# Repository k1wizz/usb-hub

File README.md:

# Usb hub
first try at usb hub using fallout tutorial
https://fallout.hackclub.com/docs/guided-projects/usb-hub
ps i made this on kicad instead of easyeda rahh

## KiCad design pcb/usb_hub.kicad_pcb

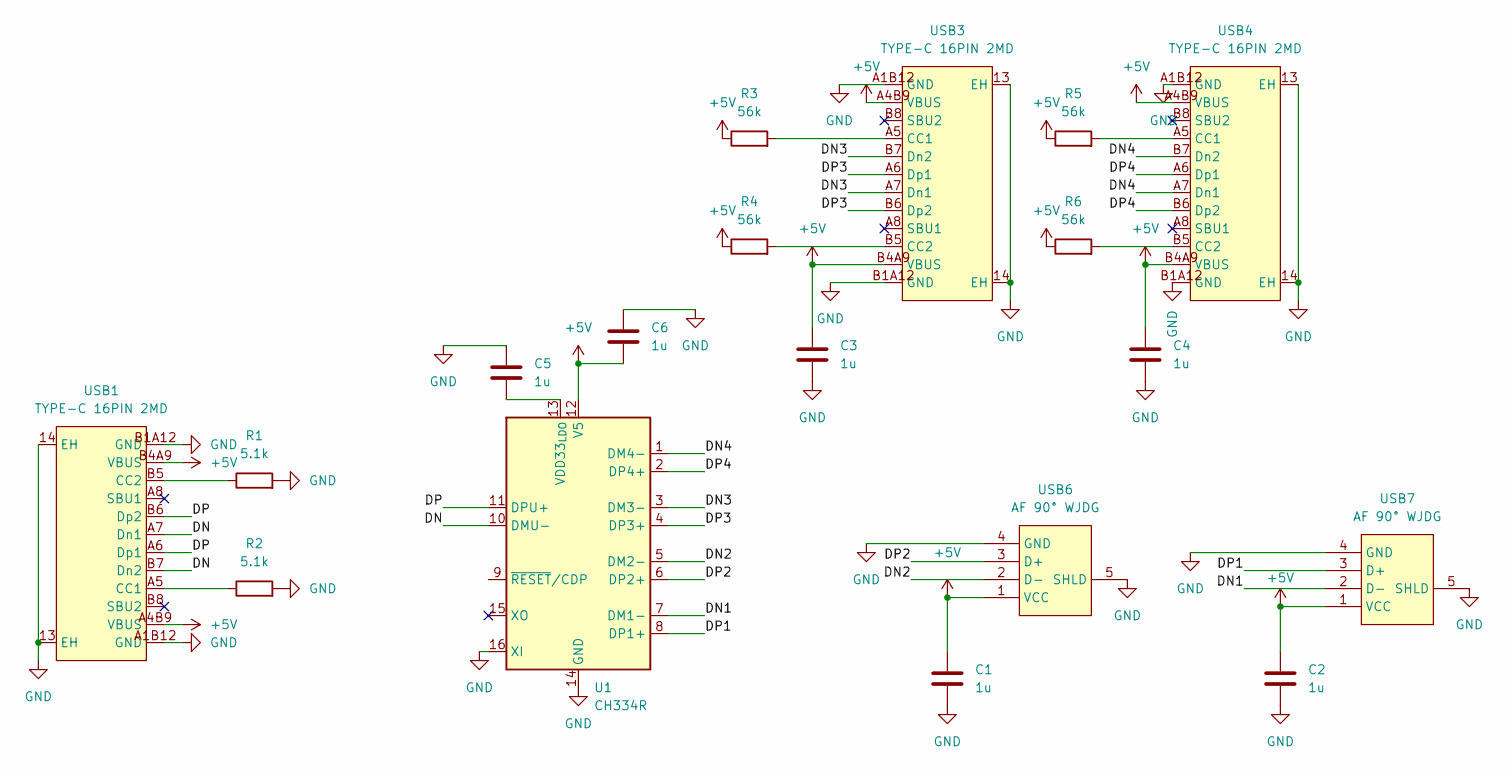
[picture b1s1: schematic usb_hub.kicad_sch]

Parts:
C1, C2, C3, C4, C5, C6: 1u; C_0603_1608Metric
R1, R2: 5.1k; R_0603_1608Metric
R3, R4, R5, R6: 56k; R_0603_1608Metric
U1: CH334R; QSOP-16_3.9x4.9mm_P0.635mm
USB1, USB3, USB4: TYPE-C 16PIN 2MD; USB-C-SMD_TYPE-C-16PIN-2MD-073; MPN TYPE-C 16PIN 2MD(073); LCSC Part C2765186
USB6, USB7: AF 90° WJDG; USB-A-TH_AF-WJDG; MPN AF 90° WJDG; LCSC Part C456018

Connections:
+5V: C1.1, C2.1, C3.1, C4.1, C6.1, R3.1, R4.1, R5.1, R6.1, U1.12 (V5), USB1.A4B9 (VBUS), USB1.B4A9 (VBUS), USB3.A4B9 (VBUS), USB3.B4A9 (VBUS), USB4.A4B9 (VBUS), USB4.B4A9 (VBUS), USB6.1 (VCC), USB7.1 (VCC)
/DN: U1.10 (DMU-), USB1.A7 (Dn1), USB1.B7 (Dn2)
/DN1: U1.7 (DM1-), USB7.2 (D-)
/DN2: U1.5 (DM2-), USB6.2 (D-)
/DN3: U1.3 (DM3-), USB3.A7 (Dn1), USB3.B7 (Dn2)
/DN4: U1.1 (DM4-), USB4.A7 (Dn1), USB4.B7 (Dn2)
/DP: U1.11 (DPU+), USB1.A6 (Dp1), USB1.B6 (Dp2)
/DP1: U1.8 (DP1+), USB7.3 (D+)
/DP2: U1.6 (DP2+), USB6.3 (D+)
/DP3: U1.4 (DP3+), USB3.A6 (Dp1), USB3.B6 (Dp2)
/DP4: U1.2 (DP4+), USB4.A6 (Dp1), USB4.B6 (Dp2)
GND: C1.2, C2.2, C3.2, C4.2, C5.2, C6.2, R1.2, R2.2, U1.14 (GND), U1.16 (XI), USB1.13 (EH), USB1.14 (EH), USB1.A1B12 (GND), USB1.B1A12 (GND), USB3.13 (EH), USB3.14 (EH), USB3.A1B12 (GND), USB3.B1A12 (GND), USB4.13 (EH), USB4.14 (EH), USB4.A1B12 (GND), USB4.B1A12 (GND), USB6.4 (GND), USB6.5 (SHLD), USB7.4 (GND), USB7.5 (SHLD)
unnamed: C5.1, U1.13 (VDD33_{LDO})
unnamed: R2.1, USB1.A5 (CC1)
unnamed: R1.1, USB1.B5 (CC2)
unnamed: R3.2, USB3.A5 (CC1)
unnamed: R4.2, USB3.B5 (CC2)
unnamed: R5.2, USB4.A5 (CC1)
unnamed: R6.2, USB4.B5 (CC2)

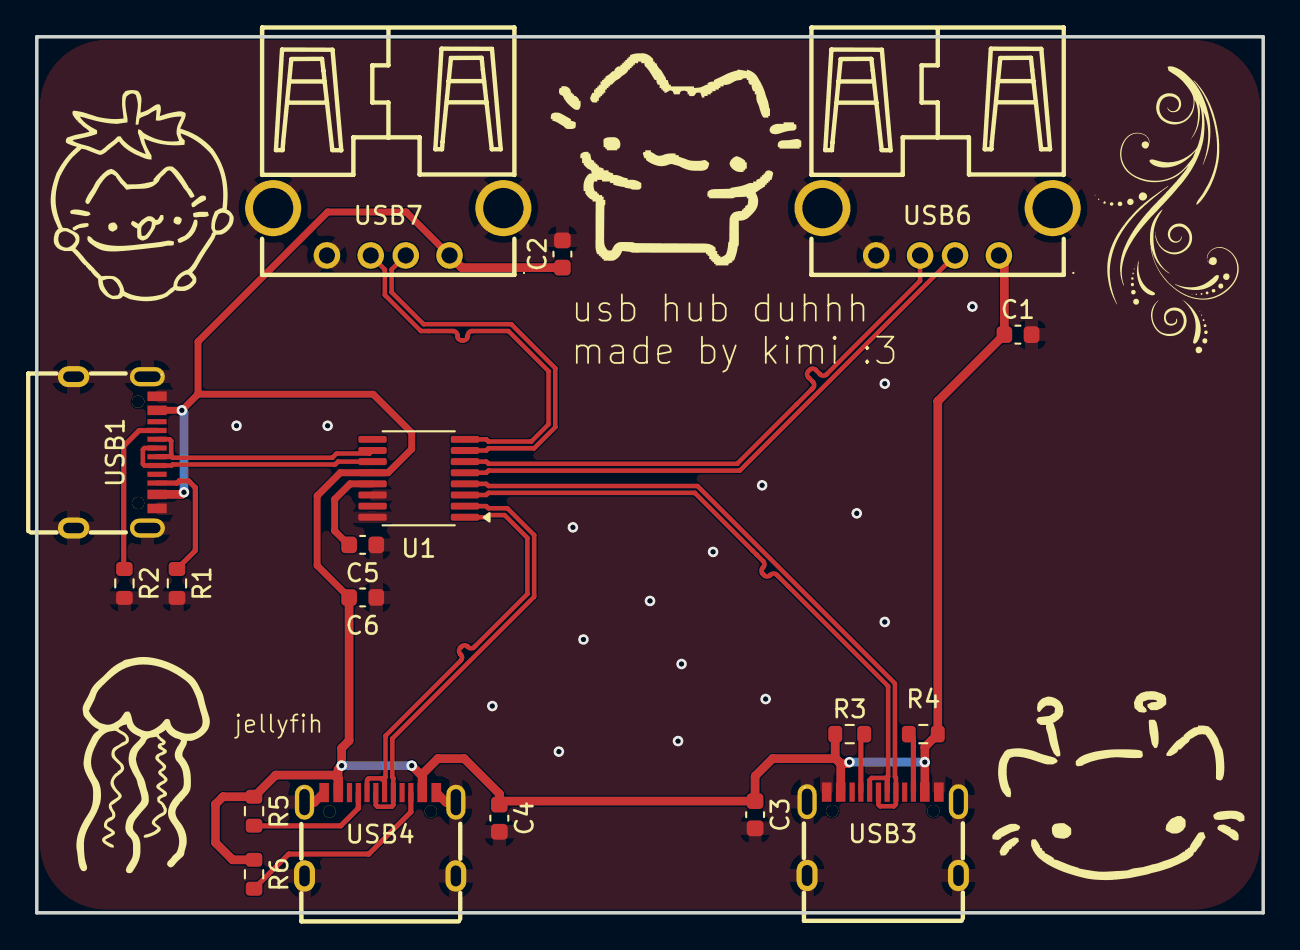
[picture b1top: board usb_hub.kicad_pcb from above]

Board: 2 copper layers, 70.0 x 50.0 mm, 18 parts (0 on the bottom side), 19 nets.
